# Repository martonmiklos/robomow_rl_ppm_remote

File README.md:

# RC Remote control for Robomow RL series lawn mowers

## What?

Quick and dirty Arduino code to being able to control your Robomow RL series mower* with a PPM remote.

*= Tested with Robomow City 120 ~~however likely to work with RL-1000, RL-2000 RL-550, RL-850, etc. which has similar removable terminal with pigtail cable.~~  It is possible that similar mowers are compatible, however RL-500 is known to be using a different protocol.

# Necessary equipment

 * PPM compatible RC transmitter an receiver (tested with a DJI Phantom MK1 remote an receiver)
 * Arduino Pro micro (the code shall be portable to other Arduinos)
 * Inverter to the Arduino TX line
 * [PPM-reader library from Nikkilae](https://github.com/Nikkilae/PPM-reader)
 
# Connection info - [see schematic in cad folder](https://raw.githubusercontent.com/martonmiklos/robomow_rl_ppm_remote/master/cad/pro_micro_adapter_schematic.pdf)

 * Hook your PPM receiever's output to the Arduino's pin 3
 * Remove the terminal from the mower
 * Connect your Serial1 port TX pin to the RX pin of mower's terminal RJ11 (pin 5)
 * Power your Arduino and the mower
 * Profit!

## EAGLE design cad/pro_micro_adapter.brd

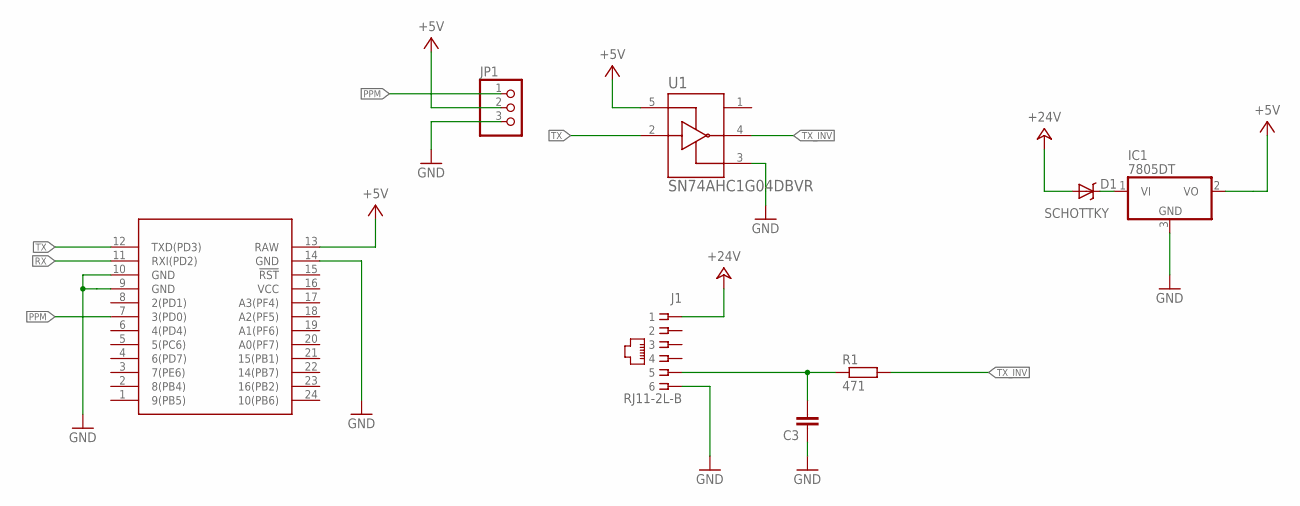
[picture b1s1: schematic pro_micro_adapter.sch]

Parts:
C3: C-EUC0805; C0805
D1: SCHOTTKY; DO-214AC
IC1: 7805DT; TO252
J1: RJ11-2L-B; RJ11-NO_SHIELD
JP1: PINHD-1X3; 1X03
R1: 471; R0805
U1: SN74AHC1G04DBVR; SOT95P280X145-5N
U$1: ARDUINO_MICRO_PRO

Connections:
+5V: IC1.2 (VO), JP1.2, U1.5 (VCC), U$1.13 (RAW)
+24V: D1.A, J1.1
GND: C3.1, IC1.3 (GND), J1.6, JP1.3, U1.3 (GND), U$1.9 (GND), U$1.10 (GND), U$1.14 (GND)
unnamed: D1.C, IC1.1 (VI)
PPM: JP1.1, U$1.7 (3(PD0))
RX: U$1.11 (RXI(PD2))
TX: U1.2 (A), U$1.12 (TXD(PD3))
TX_INV: R1.2, U1.4 (Y)
TX_R: C3.2, J1.5, R1.1
VCC: U$1.16 (VCC)

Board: 2 copper layers, 8 parts (2 on the bottom side), 8 nets, no tracks yet.

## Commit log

2021-11-02 Added readme
2021-11-04 Update README.md
    Mention inverter
2022-01-16 Added EAGLE schematics
2022-01-16 Do not allow more buttons to be pressed while turning on the mowing
2022-01-16 Readme pimp
2022-02-16 Rearranged sch for better readability
2022-04-15 Fix TX pin number in readme
2023-04-30 - Do not stop movement when turning on and off mowing - Mention PPM-reader in the readme
2023-05-01 Turn off rabbit mode when start mowing
